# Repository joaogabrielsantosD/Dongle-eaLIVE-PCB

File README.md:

# Dongle-eaLIVE-PCB

## Hardware
Dongle-eaLIVE has been created using KiCad and all the design files can be found under [01_Specs](01_Specs/) folder (you can see in this folder the [Schematic](01_Specs/01_Schematic/), [LayoutPCB](01_Specs/02_LayoutPCB/) and [3Dmodel](01_Specs/03_3Dmodel/)) , and the  production can be found in [Gerber](02_Gerber&BOM/01_Gerber/) files and the interactive BOM in [BOM](02_Gerber&BOM/02_BOM/00_InteractiveBOM/). Images below shows a quick overview of the hardware design.

| PCB Front           |  PCB Back |
| :-------------------------: | :-------------------------: |
|   |  |

### Dimensions

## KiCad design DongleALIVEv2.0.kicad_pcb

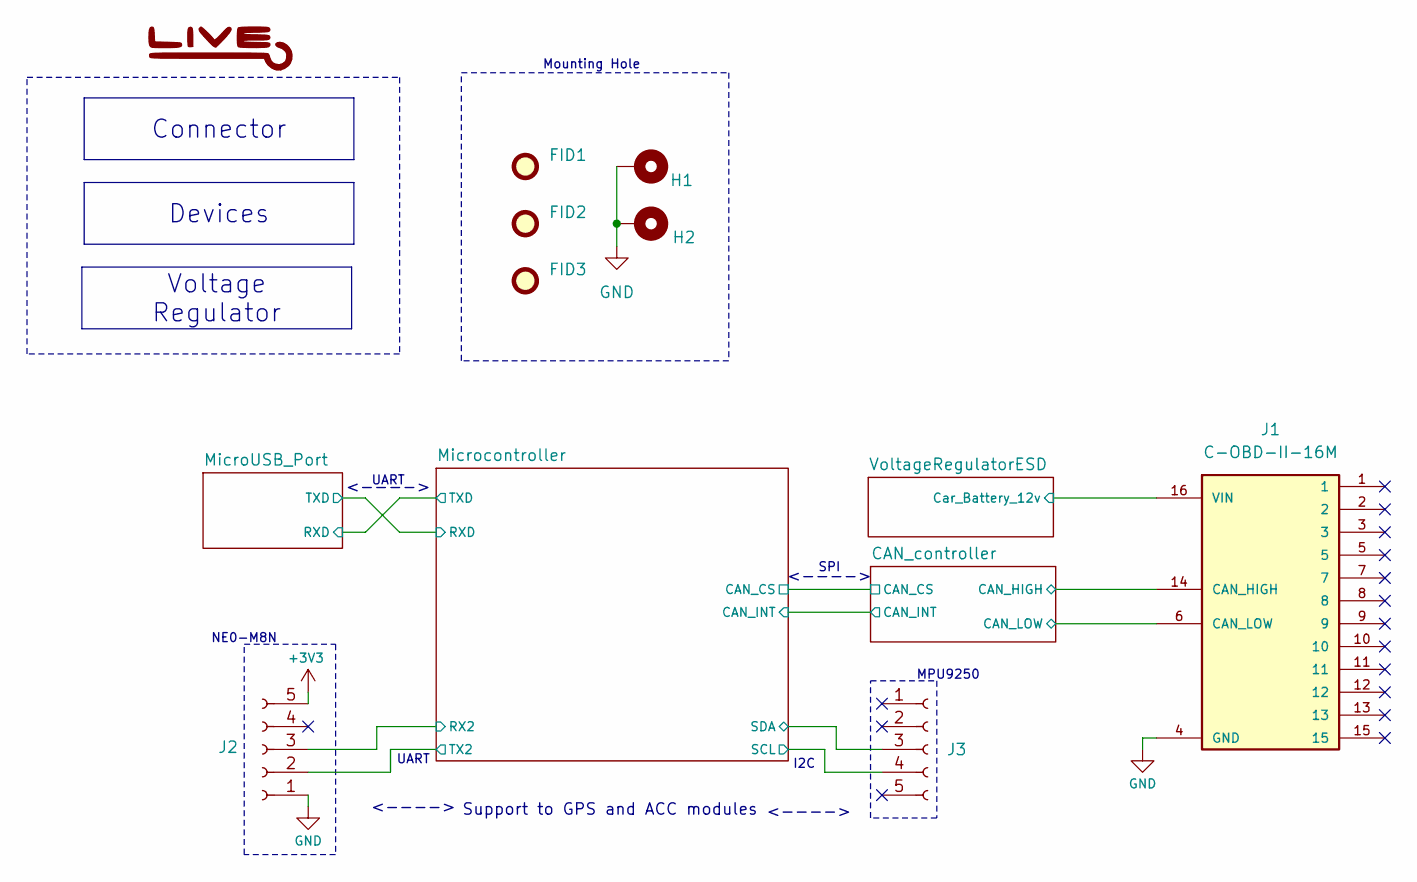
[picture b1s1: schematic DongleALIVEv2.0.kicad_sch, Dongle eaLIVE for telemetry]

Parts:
FID1, FID2, FID3: Fiducial; Fiducial_0.5mm_Mask1mm
H1, H2: MountingHole_Pad; MountingHole_2.2mm_M2_Pad_Via
J1: C-OBD-II-16M; COMTECH_C-OBD-II-16M
J2, J3: Conn_01x05_Socket; PinSocket_1x05_P2.54mm_Vertical; LCSC C16076298

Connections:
+3V3: J2.5; also elsewhere on the board
/CAN_controller/CAN_HIGH: J1.14 (CAN_HIGH); also elsewhere on the board
/CAN_controller/CAN_LOW: J1.6 (CAN_LOW); also elsewhere on the board
/Microcontroller/RX2: J2.3; also elsewhere on the board
/Microcontroller/SCL: J3.4; also elsewhere on the board
/Microcontroller/SDA: J3.3; also elsewhere on the board
/Microcontroller/TX2: J2.2; also elsewhere on the board
/VoltageRegulatorESD/Car_Battery_12v: J1.16 (VIN); also elsewhere on the board
GND: H1.1, H2.1, J1.4 (GND), J2.1; also elsewhere on the board

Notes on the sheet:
Connector
Voltage Regulator
Devices
Mounting Hole
UART
MPU9250
NE0-M8N
<---->
I2C
Support to GPS and ACC modules
SPI

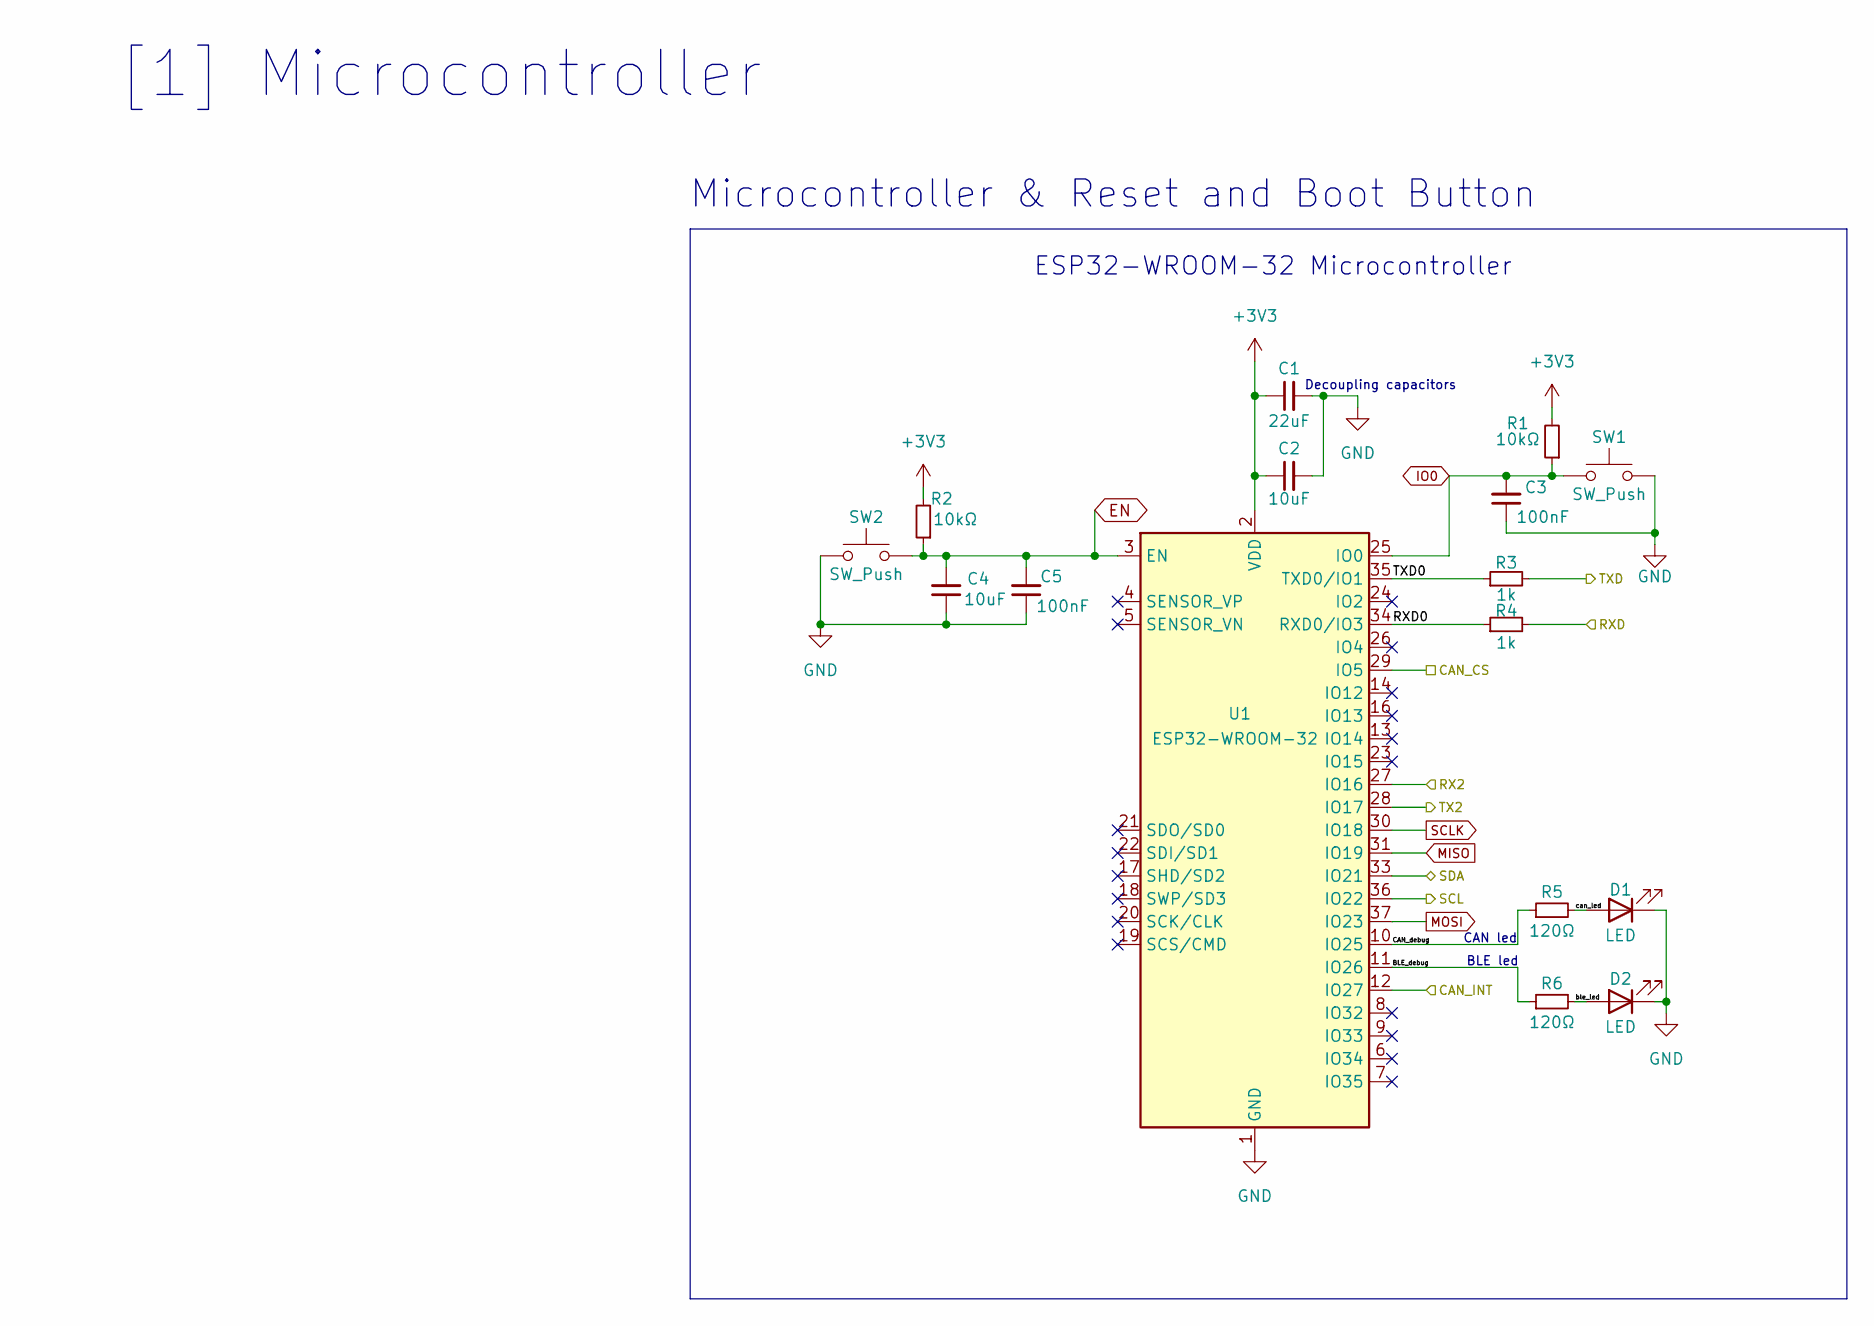
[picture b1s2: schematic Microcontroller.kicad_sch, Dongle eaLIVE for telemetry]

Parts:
C1: 22uF; C_0805_2012Metric_Pad1.18x1.45mm_HandSolder; LCSC C105484
C2, C4: 10uF; C_0805_2012Metric_Pad1.18x1.45mm_HandSolder; LCSC C15850
C3, C5: 100nF; C_0805_2012Metric_Pad1.18x1.45mm_HandSolder; LCSC C49678
D1: LED; LED_0805_2012Metric; LCSC C2296
D2: LED; LED_0805_2012Metric; LCSC C34499
R1, R2: 10kΩ; R_0805_2012Metric_Pad1.20x1.40mm_HandSolder; LCSC C191101
R3, R4: 1k; R_0805_2012Metric_Pad1.20x1.40mm_HandSolder; LCSC C17513
R5, R6: 120Ω; R_0805_2012Metric_Pad1.20x1.40mm_HandSolder; LCSC C966144
SW1, SW2: SW_Push; SW_SPST_CK_RS282G05A3; LCSC C483808
U1: ESP32-WROOM-32; LCSC C82899

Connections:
+3V3: C1.1, C2.1, R1.2, R2.2, U1.2 (VDD); also elsewhere on the board
/CAN_controller/CAN_CS: U1.29 (IO5); also elsewhere on the board
/CAN_controller/CAN_INT: U1.12 (IO27); also elsewhere on the board
/MicroUSB_Port/RXD: R3.2; also elsewhere on the board
/MicroUSB_Port/TXD: R4.2; also elsewhere on the board
/Microcontroller/BLE_debug: R6.1, U1.11 (IO26)
/Microcontroller/CAN_debug: R5.1, U1.10 (IO25)
/Microcontroller/RX2: U1.27 (IO16); also elsewhere on the board
/Microcontroller/RXD0: R4.1, U1.34 (RXD0/IO3)
/Microcontroller/SCL: U1.36 (IO22); also elsewhere on the board
/Microcontroller/SDA: U1.33 (IO21); also elsewhere on the board
/Microcontroller/TX2: U1.28 (IO17); also elsewhere on the board
/Microcontroller/TXD0: R3.1, U1.35 (TXD0/IO1)
/Microcontroller/ble_led: D2.2 (A), R6.2
/Microcontroller/can_led: D1.2 (A), R5.2
EN: C4.2, C5.2, R2.1, SW2.2, U1.3 (EN); also elsewhere on the board
GND: C1.2, C2.2, C3.1, C4.1, C5.1, D1.1 (K), D2.1 (K), SW1.2, SW2.1, U1.1 (GND), U1.15 (GND), U1.38 (GND), U1.39 (GND); also elsewhere on the board
IO0: C3.2, R1.1, SW1.1, U1.25 (IO0); also elsewhere on the board
MISO: U1.31 (IO19); also elsewhere on the board
MOSI: U1.37 (IO23); also elsewhere on the board
SCLK: U1.30 (IO18); also elsewhere on the board

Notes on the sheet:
ESP32-WROOM-32 Microcontroller
Microcontroller & Reset and Boot Button
CAN led
[1] Microcontroller
BLE led
Decoupling capacitors

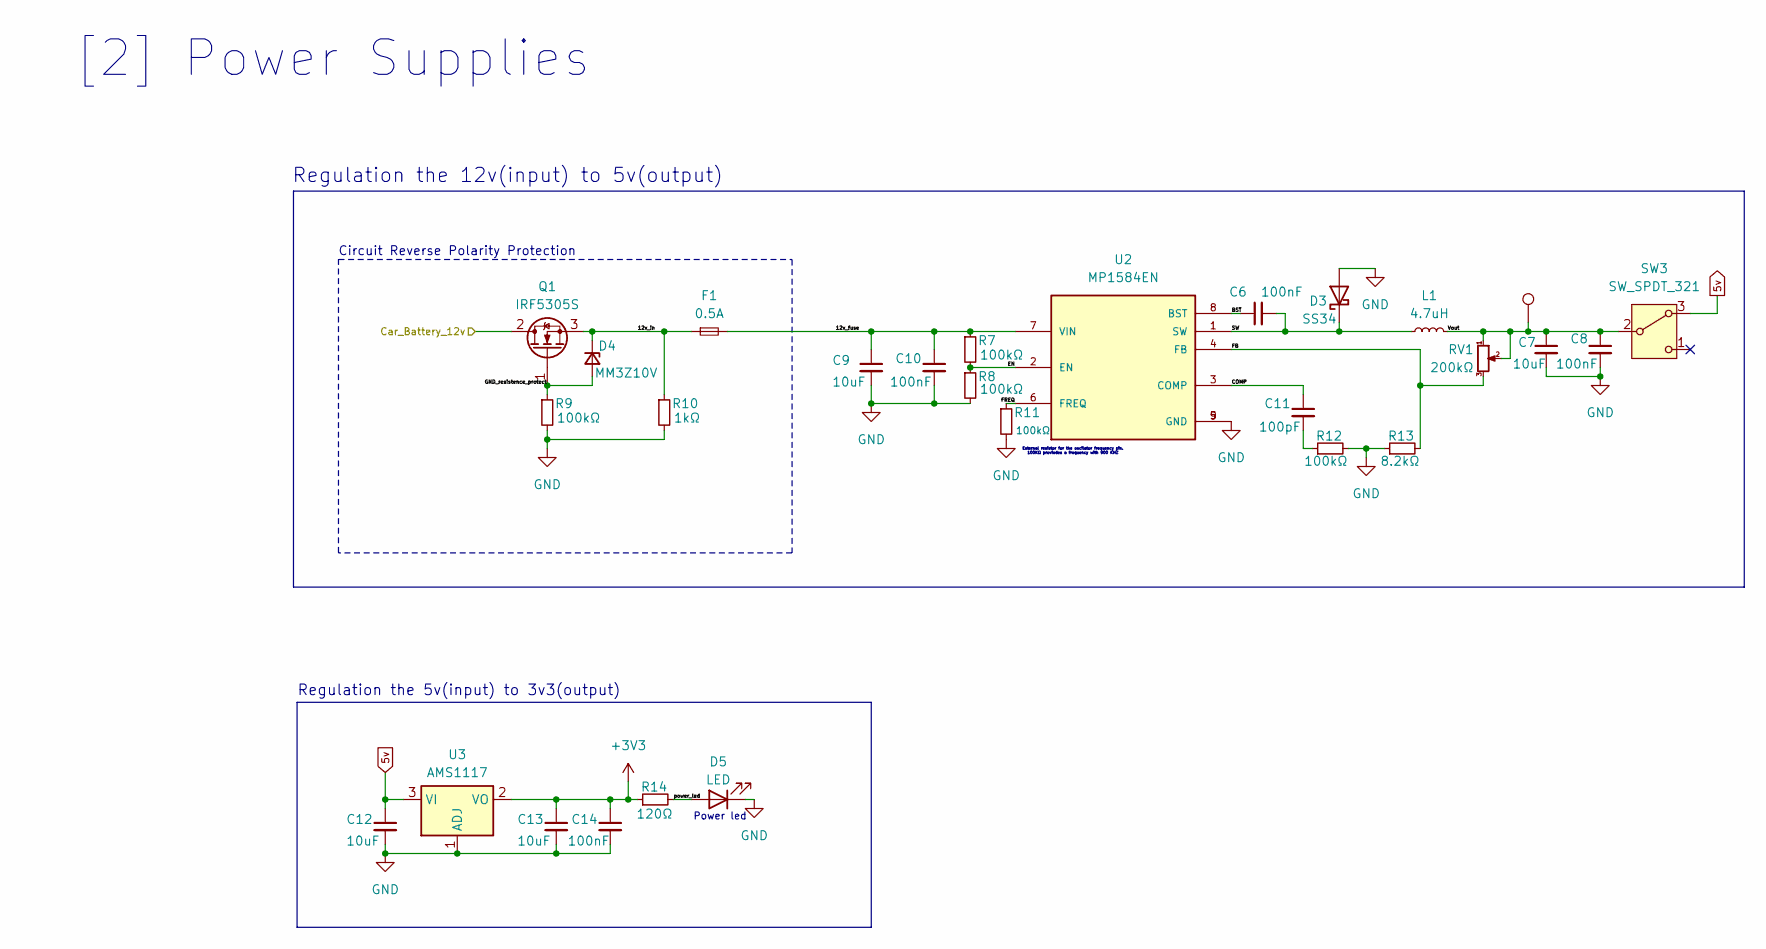
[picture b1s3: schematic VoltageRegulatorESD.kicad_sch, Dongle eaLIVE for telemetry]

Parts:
C6, C8, C10, C14: 100nF; C_0805_2012Metric_Pad1.18x1.45mm_HandSolder; LCSC C49678
C7, C9, C12, C13: 10uF; C_0805_2012Metric_Pad1.18x1.45mm_HandSolder; LCSC C15850
C11: 100pF; C_0805_2012Metric_Pad1.18x1.45mm_HandSolder; LCSC C1790
D3: SS34; LCSC C8678
D4: MM3Z10V; MM3Z10VT1G; LCSC C39057
D5: LED; LED_0805_2012Metric; LCSC C19171391
F1: 0.5A; Fuseholder_Clip-5x20mm_Littelfuse_111_Inline_P20.00x5.00mm_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
L1: 4.7uH; L_Cenker_CKCS6028; LCSC C108295
Q1: IRF5305S; LCSC C2874634
R7, R8, R9, R11, R12: 100kΩ; R_0805_2012Metric_Pad1.20x1.40mm_HandSolder; LCSC C149504
R10: 1kΩ; R_0805_2012Metric_Pad1.20x1.40mm_HandSolder; LCSC C17513
R13: 8.2kΩ; R_0805_2012Metric_Pad1.20x1.40mm_HandSolder; LCSC C17828
R14: 120Ω; R_0805_2012Metric_Pad1.20x1.40mm_HandSolder; LCSC C966144
RV1: 200kΩ; Potenciometer; LCSC C128551
SW3: SW_SPDT_321; SW_Slide_SPDT_Angled_CK_OS102011MA1Q; LCSC C273393
TP1: TestPoint; TestPoint_Pad_D1.0mm
U2: MP1584EN
U3: AMS1117; SOT-223-3_TabPin2; LCSC C917183

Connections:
5v: C12.1, SW3.3 (A), U3.3 (VI); also elsewhere on the board
+3V3: C13.1, C14.1, R14.1, U3.2 (VO); also elsewhere on the board
/VoltageRegulatorESD/12v_fuse: C9.1, C10.1, F1.2, R7.1, U2.7 (VIN)
/VoltageRegulatorESD/12v_in: D4.1 (K), F1.1, Q1.3 (S), R10.1
/VoltageRegulatorESD/BST: C6.1, U2.8 (BST)
/VoltageRegulatorESD/COMP: C11.1, U2.3 (COMP)
/VoltageRegulatorESD/Car_Battery_12v: Q1.2 (D); also elsewhere on the board
/VoltageRegulatorESD/EN: R7.2, R8.1, U2.2 (EN)
/VoltageRegulatorESD/FB: R13.2, RV1.3, U2.4 (FB)
/VoltageRegulatorESD/FREQ: R11.1, U2.6 (FREQ)
/VoltageRegulatorESD/GND_resistence_protect: D4.2 (A), Q1.1 (G), R9.1
/VoltageRegulatorESD/SW: C6.2, D3.1 (K), L1.1, U2.1 (SW)
/VoltageRegulatorESD/Vout: C7.1, C8.1, L1.2, RV1.1, RV1.2, SW3.2 (B), TP1.1
/VoltageRegulatorESD/power_led: D5.2 (A), R14.2
GND: C7.2, C8.2, C9.2, C10.2, C12.2, C13.2, C14.2, D3.2 (A), D5.1 (K), R8.2, R9.2, R10.2, R11.2, R12.2, R13.1, U2.5 (GND), U2.9 (GND), U3.1 (ADJ); also elsewhere on the board
unnamed: C11.2, R12.1

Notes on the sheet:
Regulation the 12v(input) to 5v(output)
[2] Power Supplies
External resistor for the oscilator frequency pin. 100KΩ proviedes a frequency with 900 KHZ
Power led
Regulation the 5v(input) to 3v3(output)
Circuit Reverse Polarity Protection

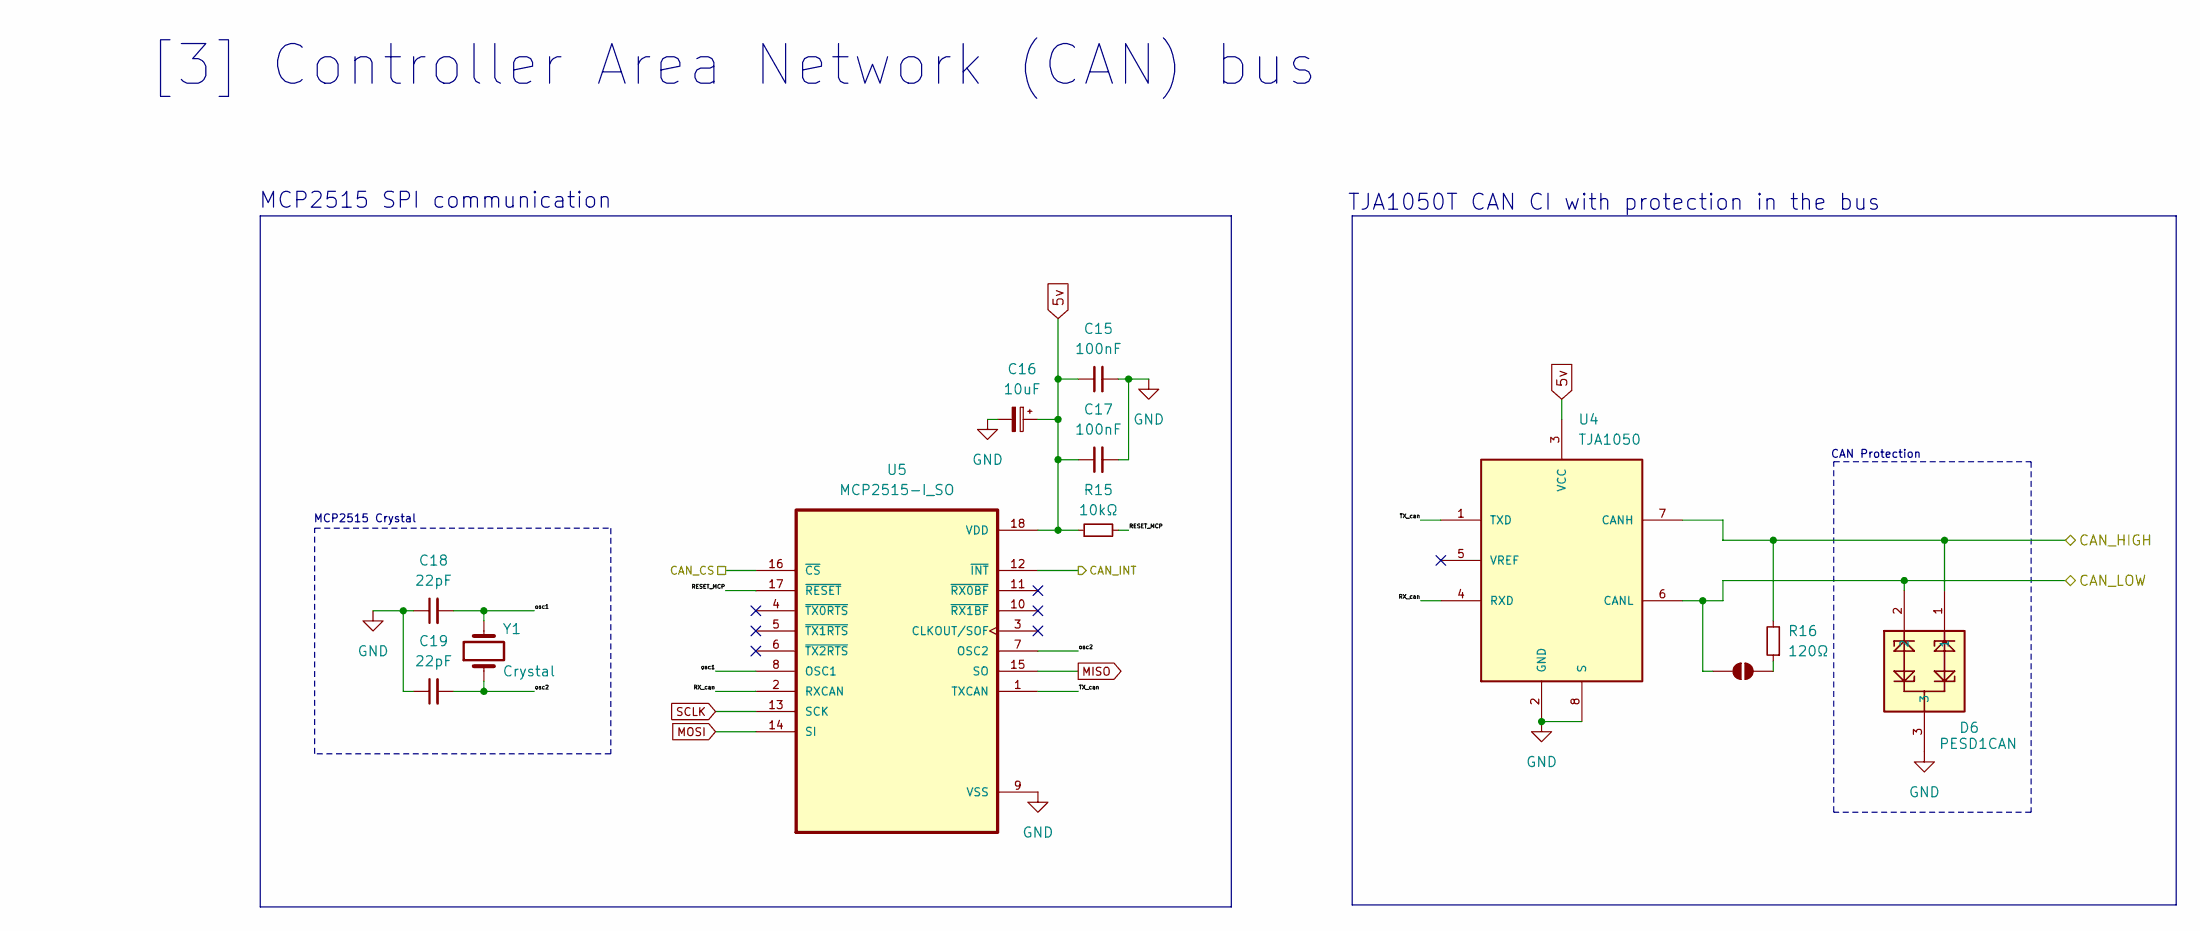
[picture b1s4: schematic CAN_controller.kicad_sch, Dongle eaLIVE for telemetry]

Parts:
C15, C17: 100nF; C_0805_2012Metric_Pad1.18x1.45mm_HandSolder; LCSC C49678
C16: 10uF; CP_EIA-2012-12_Kemet-R_Pad1.30x1.05mm_HandSolder; LCSC C201218
C18, C19: 22pF; C_0805_2012Metric_Pad1.18x1.45mm_HandSolder; LCSC C157623
D6: PESD1CAN; LCSC C343993
JP1: SolderJumper_2_Open; SolderJumper-2_P1.3mm_Open_RoundedPad1.0x1.5mm
R15: 10kΩ; R_0805_2012Metric_Pad1.20x1.40mm_HandSolder; LCSC C191101
R16: 120Ω; R_0805_2012Metric_Pad1.20x1.40mm_HandSolder; LCSC C966144
U4: TJA1050; TJA1050T; LCSC C6952
U5: MCP2515-I_SO; MCP2515; LCSC C5250735
Y1: Crystal; Crystal_SMD_HC49-SD; LCSC C252310

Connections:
5v: C15.1, C16.1, C17.1, R15.1, U4.3 (VCC), U5.18 (VDD); also elsewhere on the board
/CAN_controller/CAN_CS: U5.16 (~CS); also elsewhere on the board
/CAN_controller/CAN_HIGH: D6.1, R16.2, U4.7 (CANH); also elsewhere on the board
/CAN_controller/CAN_INT: U5.12 (~INT); also elsewhere on the board
/CAN_controller/CAN_LOW: D6.2, JP1.1 (A), U4.6 (CANL); also elsewhere on the board
/CAN_controller/RESET_MCP: R15.2, U5.17 (~RESET)
/CAN_controller/RX_can: U4.4 (RXD), U5.2 (RXCAN)
/CAN_controller/TX_can: U4.1 (TXD), U5.1 (TXCAN)
/CAN_controller/osc1: C18.2, U5.8 (OSC1), Y1.2
/CAN_controller/osc2: C19.2, U5.7 (OSC2), Y1.1
GND: C15.2, C16.2, C17.2, C18.1, C19.1, D6.3, U4.2 (GND), U4.8 (S), U5.9 (VSS); also elsewhere on the board
MISO: U5.15 (SO); also elsewhere on the board
MOSI: U5.14 (SI); also elsewhere on the board
unnamed: JP1.2 (B), R16.1
SCLK: U5.13 (SCK); also elsewhere on the board

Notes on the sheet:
MCP2515 Crystal
MCP2515 SPI communication
TJA1050T CAN CI with protection in the bus
[3] Controller Area Network (CAN) bus
CAN Protection

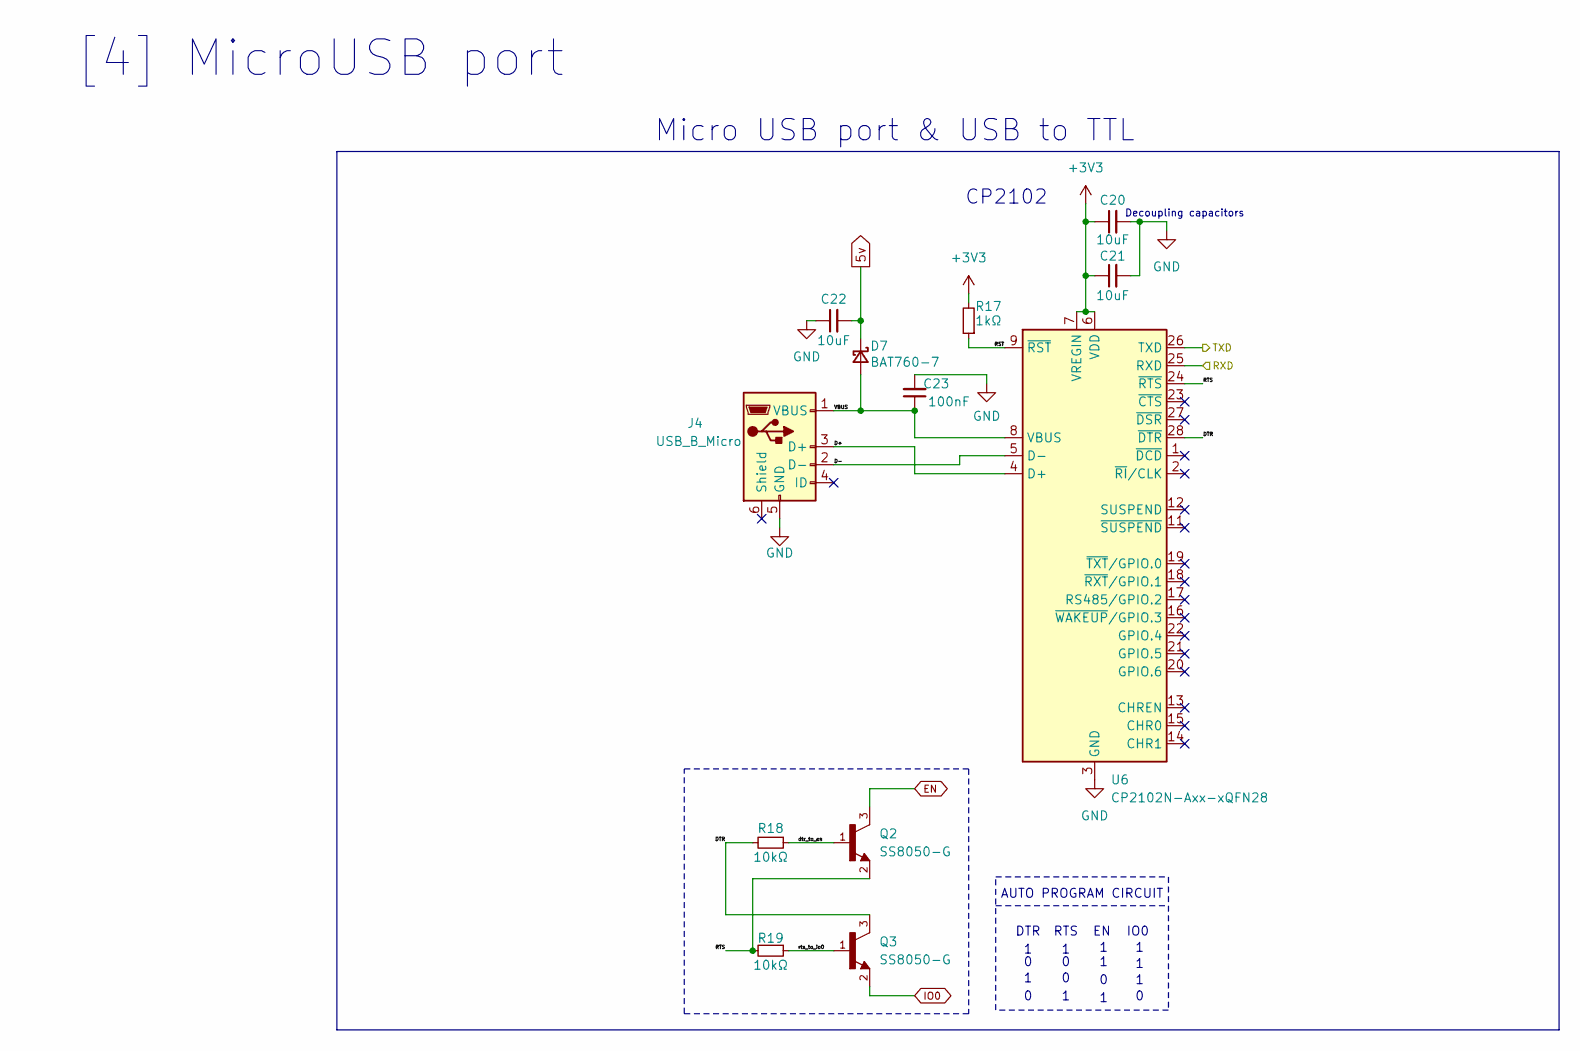
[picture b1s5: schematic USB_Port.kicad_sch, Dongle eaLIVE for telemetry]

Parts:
C20, C21, C22: 10uF; C_0805_2012Metric_Pad1.18x1.45mm_HandSolder; LCSC C15850
C23: 100nF; C_0805_2012Metric_Pad1.18x1.45mm_HandSolder; LCSC C49678
D7: BAT760-7; LCSC C124187
J4: USB_B_Micro; USB_Micro-B_Molex_47346-0001; LCSC C404968
Q2, Q3: SS8050-G; TRANS_SS8050-G; PARTREV A; LCSC C164885
R17: 1kΩ; R_0805_2012Metric_Pad1.20x1.40mm_HandSolder; LCSC C17513
R18, R19: 10kΩ; R_0805_2012Metric_Pad1.20x1.40mm_HandSolder; LCSC C191101
U6: CP2102N-Axx-xQFN28; QFN-28-1EP_5x5mm_P0.5mm_EP3.35x3.35mm; LCSC C964632

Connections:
5v: C22.2, D7.1 (K); also elsewhere on the board
+3V3: C20.1, C21.1, R17.2, U6.6 (VDD), U6.7 (VREGIN); also elsewhere on the board
/MicroUSB_Port/D+: J4.3 (D+), U6.4 (D+)
/MicroUSB_Port/D-: J4.2 (D-), U6.5 (D-)
/MicroUSB_Port/DTR: Q3.3, R18.2, U6.28 (~DTR)
/MicroUSB_Port/RST: R17.1, U6.9 (~RST)
/MicroUSB_Port/RTS: Q2.2, R19.2, U6.24 (~RTS)
/MicroUSB_Port/RXD: U6.25 (RXD); also elsewhere on the board
/MicroUSB_Port/TXD: U6.26 (TXD); also elsewhere on the board
/MicroUSB_Port/VBUS: C23.1, D7.2 (A), J4.1 (VBUS), U6.8 (VBUS)
/MicroUSB_Port/dtr_to_en: Q2.1, R18.1
/MicroUSB_Port/rts_to_io0: Q3.1, R19.1
EN: Q2.3; also elsewhere on the board
GND: C20.2, C21.2, C22.1, C23.2, J4.5 (GND), U6.3 (GND), U6.29 (GND); also elsewhere on the board
IO0: Q3.2; also elsewhere on the board

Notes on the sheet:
IO0
RTS
Decoupling capacitors
DTR
AUTO PROGRAM CIRCUIT
[4] MicroUSB port
CP2102
Micro USB port & USB to TTL

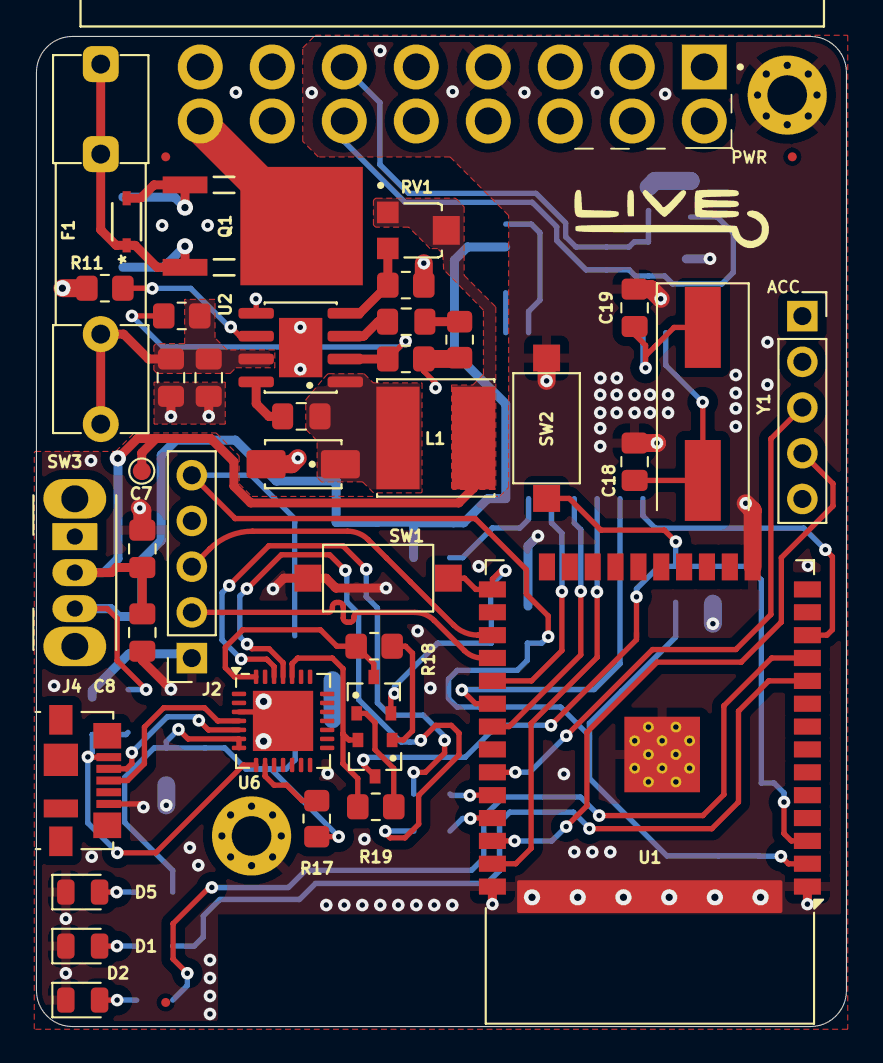
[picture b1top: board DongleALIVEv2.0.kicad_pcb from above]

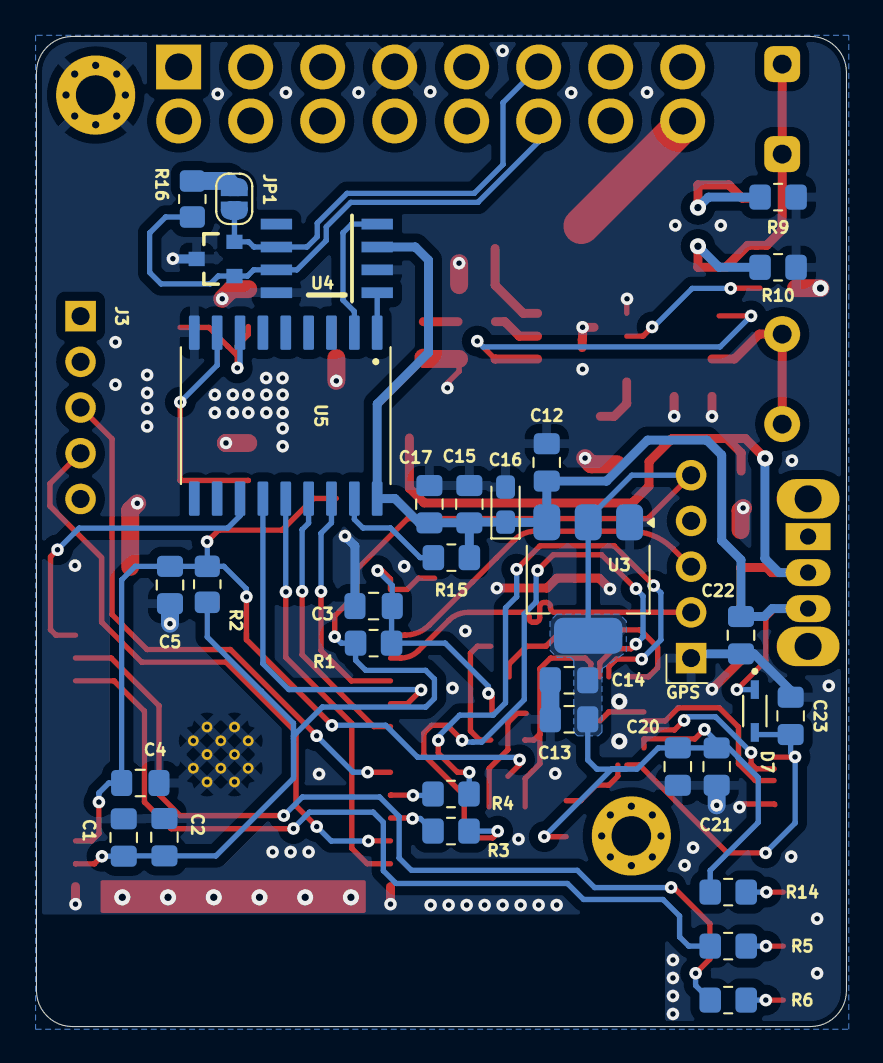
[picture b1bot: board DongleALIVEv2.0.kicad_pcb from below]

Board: 2 copper layers, 45.0 x 55.0 mm, 76 parts (32 on the bottom side), 51 nets.

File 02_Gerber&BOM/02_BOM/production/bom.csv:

Designator,Footprint,Quantity,Value,LCSC Part #
C1,0805,1,22uF,
"C10, C14, C23, C3, C5, C6, C8",0805,7,100nF,
C11,0805,1,100pF,
"C12, C13, C2, C20, C21, C22, C4, C7, C9",0805,9,10uF,
"C15, C17",0805,2,0.1uF,
C16,CP_EIA-1608-08_AVX-J_Pad1.25x1.05mm_HandSolder,1,10uF,
"C18, C19",0805,2,22pF,
"D1, D2, D5",0805,3,LED,
D3,SS34,1,SS34,
D4,MM3Z10VT1G,1,MM3Z10V,
D6,PESD1CAN,1,PESD1CAN,
D7,BAT760-7,1,BAT760-7,
F1,Fuseholder_Clip-5x20mm_Littelfuse_111_Inline_P20.00x5.00mm_D1.05mm_Horizontal,1,0.5A,
J1,COMTECH_C-OBD-II-16M,1,C-OBD-II-16M,
"J2, J3",PinSocket_1x05_P2.54mm_Vertical,2,Conn_01x05_Socket,
J4,USB_Micro-B_Molex_47346-0001,1,USB_B_Micro,
L1,L_Cenker_CKCS6028,1,4.7uH,
Q1,IRF5305S,1,IRF5305S,
"Q2, Q3",TRANS_SS8050-G,2,SS8050-G,
"R1, R15, R18, R19, R2",0805,5,10kΩ,
"R10, R17",0805,2,1kΩ,
"R11, R12, R7, R8, R9",0805,5,100kΩ,
R13,0805,1,8.2kΩ,
"R14, R16, R5, R6",0805,4,120Ω,
"R3, R4",0805,2,1k,
RV1,Potenciometer,1,200kΩ,
"SW1, SW2",SW_SPST_CK_RS282G05A3,2,SW_Push,
SW3,SW_Slide_SPDT_Angled_CK_OS102011MA1Q,1,SW_SPDT_321,
U1,ESP32-WROOM-32,1,ESP32-WROOM-32,
U2,MP1584EN,1,MP1584EN,
U3,SOT-223-3_TabPin2,1,AMS1117,
U4,TJA1050T,1,TJA1050,
U5,MCP2515,1,MCP2515-I_SO,
U6,QFN-28-1EP_5x5mm_P0.5mm_EP3.35x3.35mm,1,CP2102N-Axx-xQFN28,
Y1,Crystal_SMD_HC49-SD,1,Crystal,

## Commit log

2024-09-21 Layout Complete without BOM
2024-09-22 Fix tantalum capacitor & JLCPCB codes
2024-09-22 Testpoint to Vout
2024-09-24 Add step file of the PCB
2024-10-02 Fix CP2102 connection
2024-10-02 Update 01_Specs and Gerber
2024-10-03 45x55mm Finished
2024-10-05 Complete
2024-11-02 V1 finished
2024-11-02 photos to README
